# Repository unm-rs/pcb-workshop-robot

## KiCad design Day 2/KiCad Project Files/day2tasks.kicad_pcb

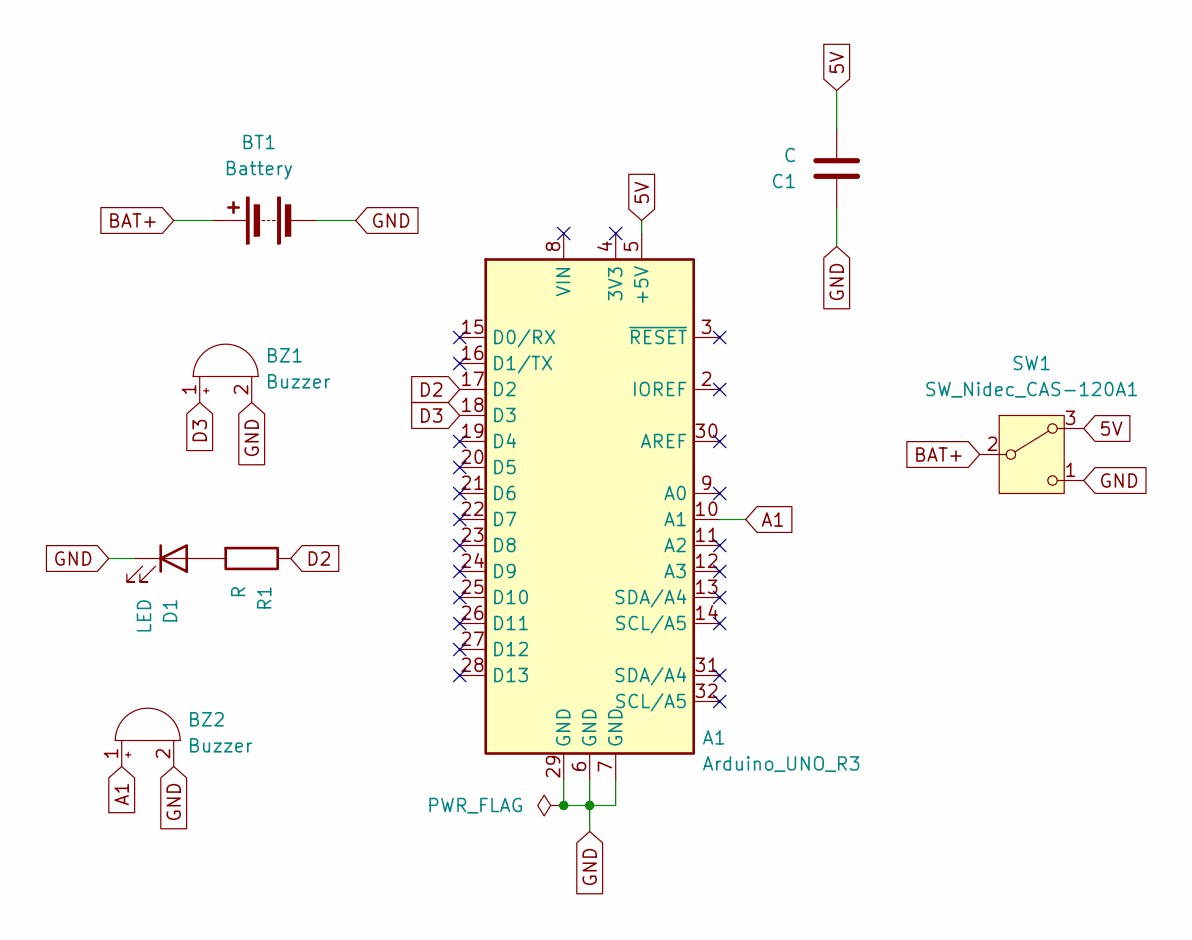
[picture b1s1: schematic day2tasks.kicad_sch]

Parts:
A1: Arduino_UNO_R3
BT1: Battery; BatteryHolder_Keystone_1057_1x2032
BZ1, BZ2: Buzzer; Buzzer_15x7.5RM7.6
C1: C; C_Axial_L3.8mm_D2.6mm_P10.00mm_Horizontal
D1: LED; LED_D3.0mm_Horizontal_O1.27mm_Z2.0mm
R1: R; R_Axial_DIN0204_L3.6mm_D1.6mm_P5.08mm_Vertical
SW1: SW_Nidec_CAS-120A1; Nidec_Copal_CAS-120A

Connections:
5V: A1.5 (+5V), C1.2, SW1.3 (A)
A1: A1.10 (A1), BZ2.1 (+)
BAT+: BT1.1 (+), SW1.2 (B)
D2: A1.17 (D2), R1.1
D3: A1.18 (D3), BZ1.1 (+)
GND: A1.6 (GND), A1.7 (GND), A1.29 (GND), BT1.2 (-), BZ1.2 (-), BZ2.2 (-), C1.1, D1.1 (K), SW1.1 (C)
unnamed: D1.2 (A), R1.2

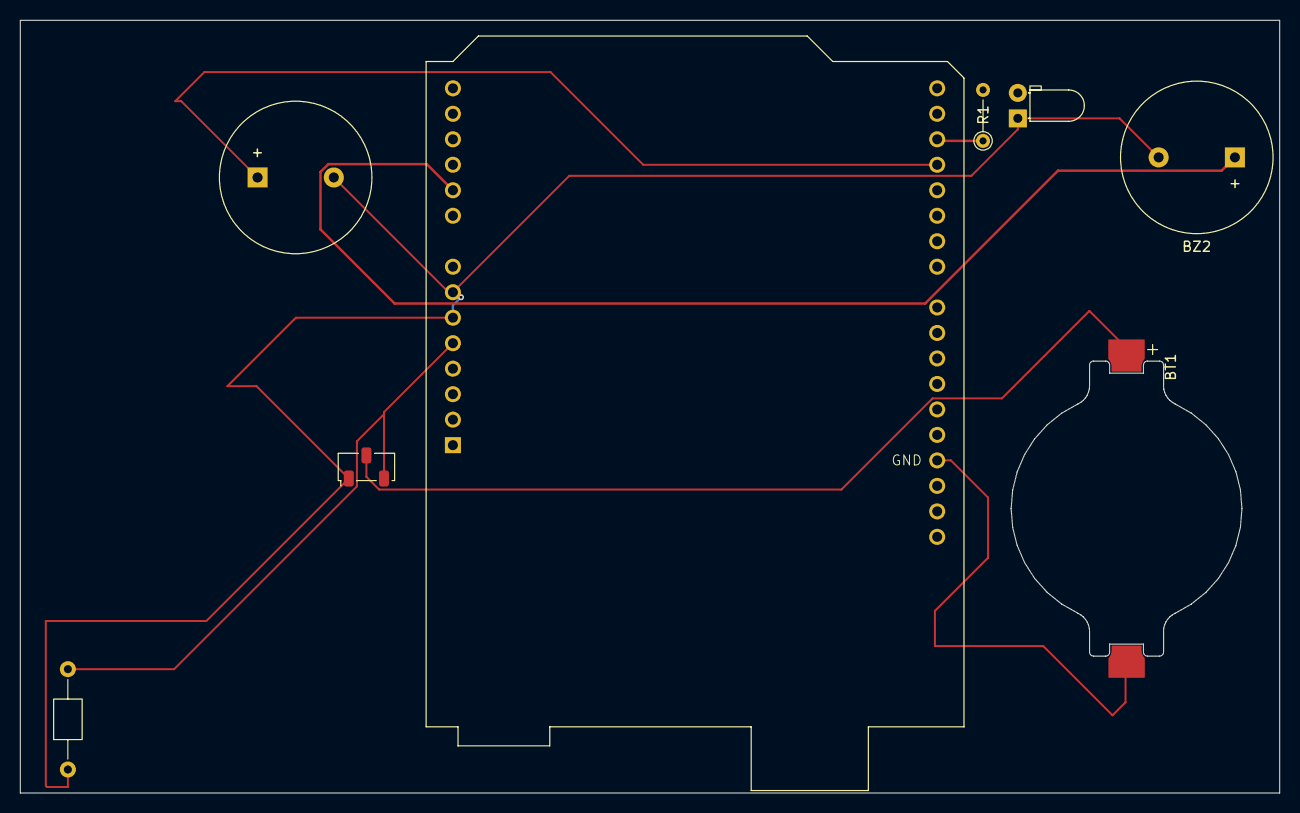
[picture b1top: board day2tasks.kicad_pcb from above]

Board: 2 copper layers, 125.4 x 76.9 mm, 8 parts (0 on the bottom side), 7 nets.

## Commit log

2026-03-21 Empty Text file
2026-03-21 STEP EPF LEAK
2026-03-21 added Day 2 and Day 3
2026-03-21 added Day 1
2026-03-25 Day 2 project files added
2026-03-25 Code for prototype
2026-04-02 Symbols & Footprints
    Uploaded symbols and footprints used for Day 3
2026-04-02 code for pcb
2026-04-02 Add ui.h header file with display functions
2026-04-02 Add facial expression drawing functions
